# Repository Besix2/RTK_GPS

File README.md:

# RTK_GPS
A RTK GPS sensor Board for drones based around the Quectel LC29H Chip. It should offer accuracy of up to 5cm. It needs a Basestation or (depending on your country) position correcting GPS data that is send to the esp32.

For a more detailed write up you can check out the journal at [Blueprint](https://blueprint.hackclub.com/projects/7904).

## Why?
I made the project because I wanted to develop a drone and needed high precission and noticed that any available solutions are insanly expensive, so I came up with my own design.

## How?
I researched several different types of drone positioning systems and basically every professional use case uses RTK GPS due to its unmatched precission. I researched multiple RTK GPS modules and found none that were cheap enough/could do what I needed. So after a lot of researching I stumbled upon the quectel LC29H module that could everything I needed. It only needed some sort of correction data. I discovered that my country offers correction data via the internet so I just needed a way to serve this data to the modul over tha air. For that I decided to use an ESP32 as it already has native support for these kind of data transmissions by ardupilot. Because this arrangement needs some resistors and capacitors I designed my own Pcb.

| Designator     | Value                       | Footprint              |   Quantity |   Price | Link                                                         |   Total Price |
|:---------------|:----------------------------|:-----------------------|-----------:|--------:|:-------------------------------------------------------------|--------------:|
| C4, C5, C6     | 10uF                        | 603                    |          3 |    0.15 | JLCPCB Part                                                  |          0.45 |
| C7             | 100nF                       | 603                    |          1 |    0.05 | JLCPCB Part                                                  |          0.05 |
| D1             | LED                         | 603                    |          1 |    0.05 | JLCPCB Part                                                  |          0.05 |
| R1, R2, R5     | 10k                         | 603                    |          3 |    0.1  | JLCPCB Part                                                  |          0.3  |
| J5             | Conn_01x04_Socket           | PinHeader_1x04_P2.54mm |          1 |    0.2  | JLCPCB Part                                                  |          0.2  |
| SW1, SW2       | SW_Push                     | SW_SPST_B3S-1000       |          2 |    0.3  | JLCPCB Part                                                  |          0.6  |
| U1             | ESP32-WROOM-32E             | ESP32-WROOM-32E        |          1 |    3.5  | JLCPCB Part                                                  |          3.5  |
| U3             | AMS1117-3.3                 | SOT-223-3              |          1 |    0.25 | JLCPCB Part                                                  |          0.25 |
| GPS Antenna    | Helix Ceramic RTK Dual Band | External               |          1 |   13.59 | [Link](https://de.aliexpress.com/item/1005009918181431.html) |         13.59 |
| GPS Connector  | Generic Connector           | External               |          1 |    1.65 | [Link](https://de.aliexpress.com/item/1005005073187553.html) |          1.65 |
| Compass (U2?)  | QMC5583L                    | Module                 |          1 |    1.89 | [Link](https://de.aliexpress.com/item/1005006794324860.html) |          1.89 |
| ELRS Module    | Onboard Antenna             | Module                 |          1 |    7.69 | [Link](https://de.aliexpress.com/item/1005005236594556.html) |          7.69 |
| Cables AWG28   | Silicone Cable              | Wiring                 |          1 |    5.59 | [Link](https://de.aliexpress.com/item/1005007671008743.html) |          5.59 |
| Cables AWG24   | Silicone Cable              | Wiring                 |          1 |    7.89 | [Link](https://de.aliexpress.com/item/1005006350734418.html) |          7.89 |
| FC             | SpeedyBee F405 V3           | Fc                     |          1 |   39.39 | [Link](https://de.aliexpress.com/item/1005004868739263.html) |         39.39 |
| RTK GPS Module | Quectel LC29H (HDA)         | Module                 |          1 |   23.59 | [Link](https://de.aliexpress.com/item/1005006870751088.html) |         23.59 |

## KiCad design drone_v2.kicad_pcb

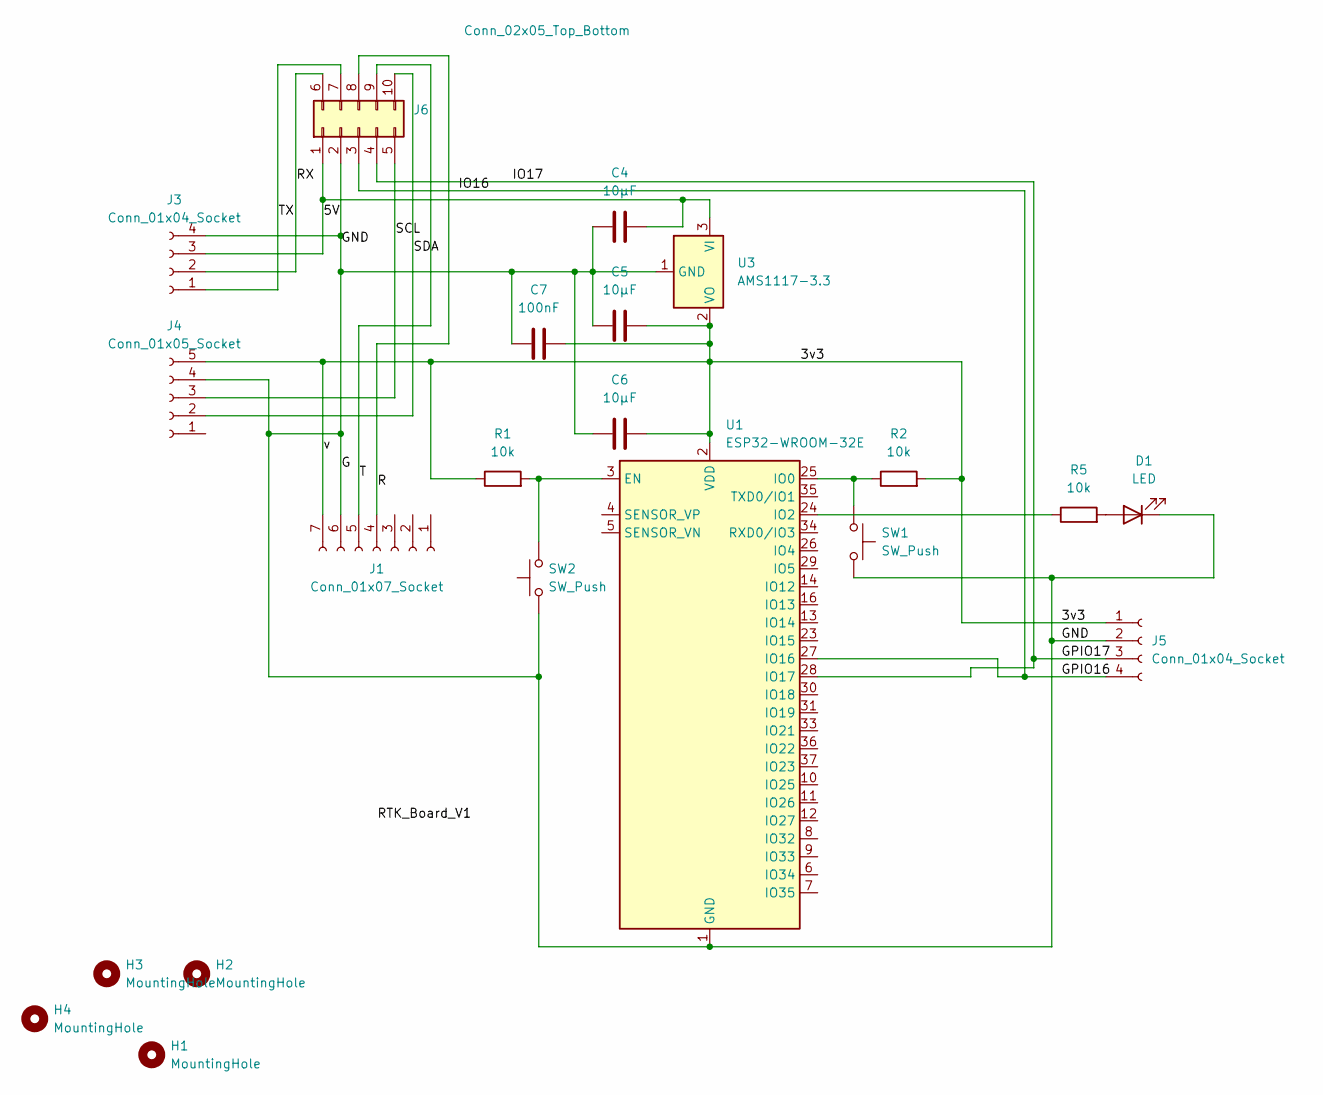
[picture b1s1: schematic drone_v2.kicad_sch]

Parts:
C4, C5, C6: 10µF; C_0603_1608Metric
C7: 100nF; C_0603_1608Metric
D1: LED; LED_0603_1608Metric
H1, H2, H3, H4: MountingHole; MountingHole_2.2mm_M2
J1: Conn_01x07_Socket; PinHeader_1x07_P2.54mm_Vertical
J3, J5: Conn_01x04_Socket; PinHeader_1x04_P2.54mm_Vertical
J4: Conn_01x05_Socket; PinHeader_1x05_P2.54mm_Vertical
J6: Conn_02x05_Top_Bottom; PinHeader_2x05_P2.54mm_Vertical
R1, R2, R5: 10k; R_0603_1608Metric
SW1, SW2: SW_Push; SW_SPST_B3S-1000
U1: ESP32-WROOM-32E
U3: AMS1117-3.3; SOT-223-3_TabPin2

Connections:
/3v3: C5.2, C6.2, C7.2, J1.7, J4.5, J5.1, R1.1, R2.2, U1.2 (VDD), U3.2 (VO)
/5V: C4.2, J3.3, J6.1, U3.3 (VI)
/G: C4.1, C5.1, C6.1, C7.1, D1.1 (K), J1.6, J3.4, J4.4, J5.2, J6.2, SW1.2, SW2.1, U1.1 (GND), U1.15 (GND), U1.38 (GND), U1.39 (GND), U3.1 (GND)
/GPIO16: J5.4, J6.3, U1.27 (IO16)
/GPIO17: J5.3, J6.4, U1.28 (IO17)
/R: J1.4, J6.8
/RX: J3.2, J6.6
/SCL: J4.3, J6.5
/SDA: J4.2, J6.10
/T: J1.5, J6.9
/TX: J3.1, J6.7
unnamed: D1.2 (A), R5.2
unnamed: R1.2, SW2.2, U1.3 (EN)
unnamed: R2.1, SW1.1, U1.25 (IO0)
unnamed: R5.1, U1.24 (IO2)

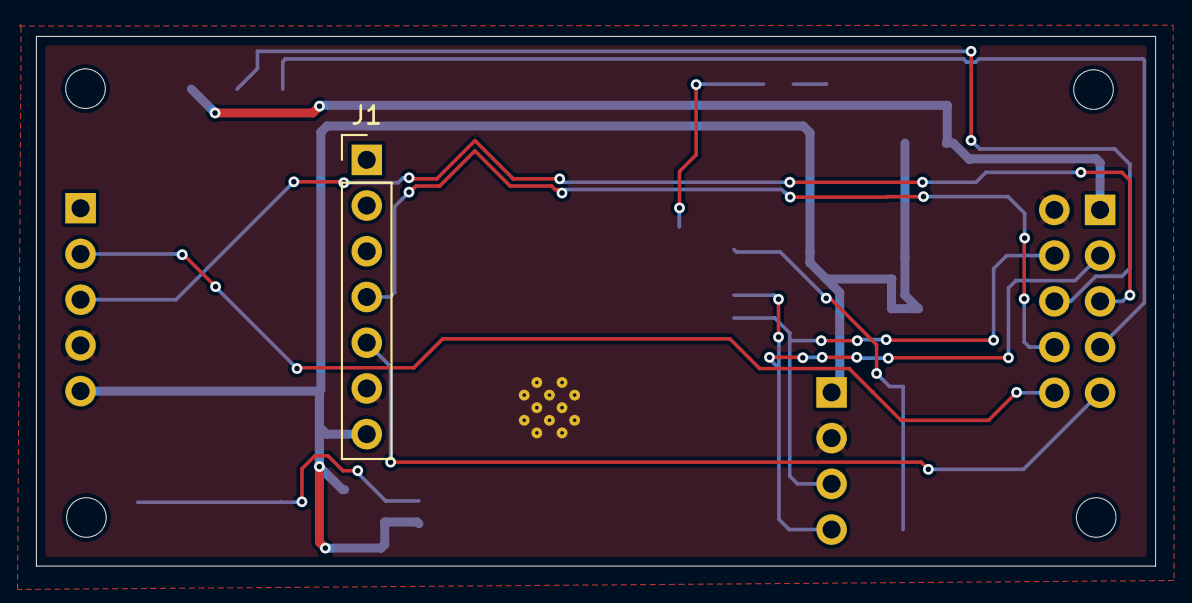
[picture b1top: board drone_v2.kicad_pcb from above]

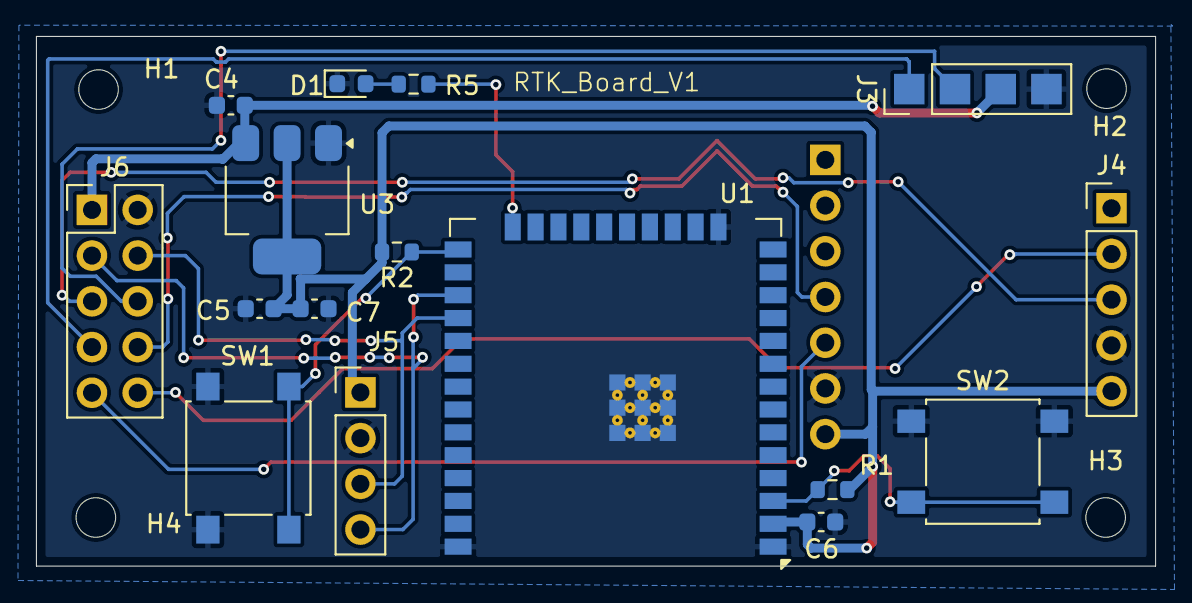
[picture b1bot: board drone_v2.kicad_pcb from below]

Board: 2 copper layers, 62.2 x 29.4 mm, 21 parts (16 on the bottom side), 15 nets.

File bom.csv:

Designator,Footprint,Quantity,Value,LCSC Part #
"C4, C5, C6",0603,3,10µF,
C7,0603,1,100nF,
D1,0603,1,LED,
J1,PinHeader_1x07_P2.54mm_Vertical,1,Conn_01x07_Socket,
"J3, J5",PinHeader_1x04_P2.54mm_Vertical,2,Conn_01x04_Socket,
J4,PinHeader_1x05_P2.54mm_Vertical,1,Conn_01x05_Socket,
J6,PinHeader_2x05_P2.54mm_Vertical,1,Conn_02x05_Top_Bottom,
"R1, R2, R5",0603,3,10k,
"SW1, SW2",SW_SPST_B3S-1000,2,SW_Push,
U1,ESP32-WROOM-32E,1,ESP32-WROOM-32E,
U3,SOT-223-3_TabPin2,1,AMS1117-3.3,

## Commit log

2025-12-26 inital
2025-12-26 Add dummy file in Gerber directory
2025-12-26 Add images to README for better visualization
    Added images to enhance the README documentation.
2025-12-28 Create dummy
2025-12-28 Enhance README with detailed sensor information
    Updated project description to include details about the Quectel LC29H Chip and accuracy specifications.
2026-02-01 Fix header format and spacing in bom.csv
    Updated the header format and corrected spacing in bom.csv.
2026-02-01 Update bom.csv formatting and component values
2026-02-03 Update BOM file with component details
    Updated the BOM file to reflect changes in component details.
2026-02-03 Add additional image and component details to README
